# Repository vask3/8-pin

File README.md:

# Mini Theremin with NE555

This is a small instrument that changes its sound depending on the light. It uses an 8-pin NE555 timer and a photoresistor. When I move my hand over the photoresistor, the shadow changes the pitch.

## How it works

The NE555 generates a signal that makes the piezo produce sound. The photoresistor changes its resistance depending on how much light hits it, which changes the frequency of the signal.

## Parts

| Part | Quantity |
|---|---:|
| NE555 in a DIP-8 package | 1 |
| 10 kΩ resistor | 2 |
| 10 nF capacitor | 2 |
| 100 nF capacitor | 1 |
| Photoresistor (LDR) | 1 |
| Passive piezo element | 1 |
| 2-pin connector | 3 |
| DIP-8 socket (optional) | 1 |

It also needs a 5 V power supply.

## Connectors

- J1 — power: pin 1 is +5V, pin 2 is GND.
- J2 — photoresistor.
- J3 — passive piezo element.

## PCB

I designed the schematic and PCB in KiCad 10. The PCB has no unconnected pads according to DRC. The photoresistor and piezo connect through separate headers, so they can be placed away from the board.

For the best effect, shine some light on the photoresistor and move your hand over it.

## Status

The PCB is designed, but it still needs to be manufactured and tested. Once it's assembled, I'll see how well it works and whether anything needs changing.

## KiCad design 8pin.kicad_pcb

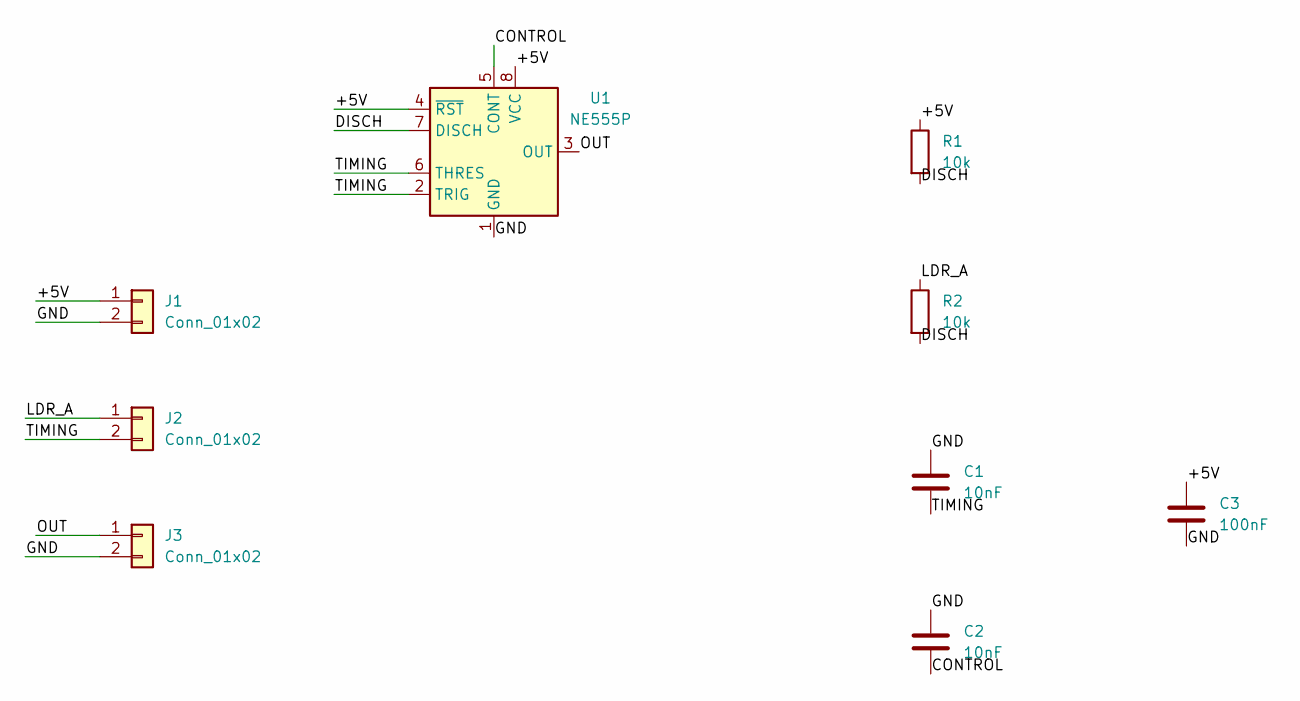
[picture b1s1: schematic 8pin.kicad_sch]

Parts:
C1, C2: 10nF; C_Disc_D5.0mm_W2.5mm_P5.00mm
C3: 100nF; C_Disc_D5.0mm_W2.5mm_P5.00mm
J1, J2, J3: Conn_01x02; PinHeader_1x02_P2.54mm_Vertical
R1, R2: 10k; R_Axial_DIN0207_L6.3mm_D2.5mm_P7.62mm_Horizontal
U1: NE555P; DIP-8_W7.62mm

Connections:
/+5V: C3.1, J1.1, R1.1, U1.4 (~RST), U1.8 (VCC)
/CONTROL: C2.2, U1.5 (CONT)
/DISCH: R1.2, R2.2, U1.7 (DISCH)
/GND: C1.1, C2.1, C3.2, J1.2, J3.2, U1.1 (GND)
/LDR_A: J2.1, R2.1
/OUT: J3.1, U1.3 (OUT)
/TIMING: C1.2, J2.2, U1.2 (TRIG), U1.6 (THRES)

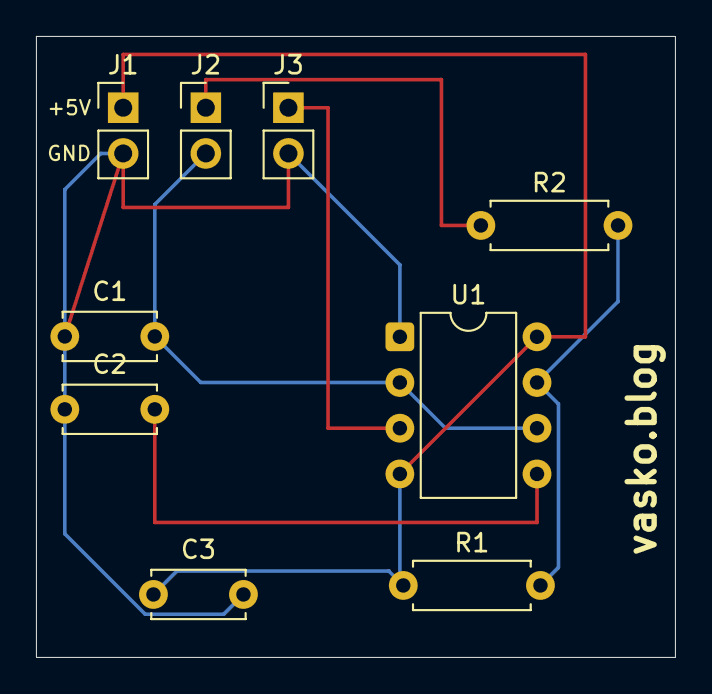
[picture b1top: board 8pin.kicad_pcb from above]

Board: 2 copper layers, 35.5 x 34.5 mm, 9 parts (0 on the bottom side), 7 nets.
